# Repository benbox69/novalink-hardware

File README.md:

# NovaLink V1

**Galvanically isolated ESP32-C3 interface for Micronova-controlled pellet stoves (NAVEL INSIDE port).**

NovaLink plugs into the 3-pin service port of a Micronova stove board (designed for X100 EVO "NAVEL INSIDE" connector,
+5 V / SER / GND, 19200 baud single-wire serial) and lets an ESP32-C3 SuperMini talk to the stove through a
3.75 kV digital isolator. The stove side is powered by the stove itself; the ESP side is powered by USB-C.
An optional VL53L0X or VL6180X (TOF050C module) time-of-flight sensor can be connected (for example to measure the pellet level).

An isolated dry-contact output (J4) drives the stove's external thermostat input (TERM), so that Home
Assistant can regulate on a room sensor placed away from the stove.

> ⚠️ **Status: V1 boards built and running on a Micronova X100 EVO: stove reading, stove control and the ToF sensor
> work. The thermostat output (J4) is not tested yet. The enclosure needs rework (see Enclosure).**
>
> This is a hobby project, not affiliated with or endorsed by Micronova. Opening a stove and connecting to its
> controller is at your own risk and may void the warranty.

## Compatibility

- **NAVEL INSIDE port** (3 pins: +5 V, SER, GND), e.g. Micronova X100 EVO: direct connection to J1.
- **SERIAL port** of other Micronova boards: should work too, through an adapter cable to J1
  (J1 pin 1 = +5 V, pin 2 = SER, pin 3 = GND). The firmware must then use the SERIAL port settings
  (usually 1200 baud, 8N2) instead of 19200 baud. Not tested yet.

> 🔴 **Never connect the 20 V line of the SERIAL port.** The SERIAL connector carries an extra supply line
> (about 15–20 V) next to +5 V, SER and GND. Only +5 V, SER and GND go to NovaLink: 20 V on J1 pin 1 would destroy
> the stove side of the board (the isolator supply is limited to 5.5 V, 6 V absolute maximum) and could damage the stove controller.
> Pin order differs between boards: identify each pin with a multimeter before wiring.

## Features

- **Isolation**: CA-IS3721HS digital isolator (Chipanalog), 3750 Vrms, 1 channel each way, fail-safe output high
  (if the ESP is unpowered, the stove line is left idle). 4 mm copper-free barrier with 1 mm milled slots under the
  isolator and under the thermostat relay (each slot runs 1.5 mm past both ends of its package to lengthen the creepage path). Separate grounds `GND_ESP` / `GND_STOVE`.
- **Stove line (SER)**: open-drain style transmit through an SS14 Schottky diode (the board only pulls SER low),
  receive through a 1 kΩ resistor. No TVS on SER on purpose: the line is only pulled up by ~38 kΩ inside the stove,
  extra capacitance would slow the edges.
- **ESP32-C3 SuperMini** (hand soldered), its edge flush with the board edge so the USB-C protrudes by 1.3 mm.
- **ToF sensor connector** (JST XH 5 pins) with 2.2 kΩ I²C pull-ups and 100 Ω series resistors on the cable lines.
- **Extension header** (7 pins, 2.54 mm): GPIO0, GPIO1, I²C, 3V3, GND, 5V (USB).
- **Status LED** on GPIO10, test points for TX, RX, 5V, SER and GND.
- **Thermostat output**: Omron G3VM-61VY3 MOSFET relay (3.75 kVrms, 60 V, 0.7 A), normally open dry contact
  on J4 for the stove TERM input, driven by GPIO3 (removed from J3).
- 89 × 30 mm, 2 layers, all SMD parts in 0805 / SOIC / SOP / SMA (hand-solderable).
- 3D-printable enclosure with captive M3 nuts, magnets and a snap-fit lid.

## Repository layout

| Path | Content |
|---|---|
| `NovaLink.kicad_*` | KiCad 10 project (schematic, PCB) |
| `libs/` | Project library: CA-IS3721HS, G3VM-61VY3 and ESP32-C3 SuperMini symbols, ESP32-C3 SuperMini footprint |
| `production/` | Manufacturing files: `NovaLink.zip` (Gerbers + drill), `bom.csv`, `positions.csv` |
| `docs/` | Schematic PDF, PCB renders, board STEP |
| `enclosure/` | Enclosure: STL, multi-colour 3MF and STEP files |

## Schematic

[docs/NovaLink_schematic.pdf](docs/NovaLink_schematic.pdf) — one A4 sheet, six blocks: ESP32-C3 SuperMini and LED,
isolation and stove connector, test points and mounting holes, ToF sensor, extension header, thermostat output.

### ESP32-C3 SuperMini pins

| Function | GPIO | Notes |
|---|---|---|
| TX to stove | GPIO5 | UART1 TX (GPIO21 is avoided: it prints the ROM boot log) |
| RX from stove | GPIO20 | UART1 RX |
| I²C SDA / SCL | GPIO6 / GPIO7 | shared between J2 and J3 |
| Sensor XSHUT | GPIO4 | |
| Status LED | GPIO10 | active high |
| Thermostat output | GPIO3 | high = contact closed |
| On J3 only | GPIO0, GPIO1 | |
| Unused | GPIO2, GPIO8, GPIO9, GPIO21 | strapping / boot pins |

### Connectors

| Ref | Type | Pinout |
|---|---|---|
| J1 (stove) | JST XH 3 pins, right angle | 1 = +5V, 2 = SER, 3 = GND (stove side, isolated) |
| J2 (ToF sensor) | JST XH 5 pins, right angle | 1 = 3V3, 2 = GND, 3 = SDA, 4 = SCL, 5 = XSHUT |
| J3 (extension) | 1×7 pin header 2.54 mm | IO0, IO1, SDA, SCL, 3V3, GND, 5V (USB, not isolated) |
| J4 (stove TERM) | JST XH 2 pins, right angle | 1, 2 = dry contact to the stove TERM input, no polarity (isolated) |

## Bill of materials

[production/bom.csv](production/bom.csv) (values, packages, LCSC part numbers). U1, the ESP32-C3 SuperMini
(U.FL version recommended), is not in the file: it is hand soldered.

## Thermostat output

Micronova boards have an external thermostat input (TERM, a normally open dry contact). On the boards documented by
Micronova (I023, N100), the contact works as follows:

| J4 contact | STAND-BY off (default) | STAND-BY on |
|---|---|---|
| Closed (GPIO3 high) | WORK at the set power | WORK |
| Open (GPIO3 low, ESP off) | MODULATION (minimum power, flame on) | MODULATION, then shutdown after Pr44, restart when the contact closes |

The stove still heats while its own room probe is below its set point (probe **or** contact). To let the contact
alone decide, set the stove set point to 7 °C; a higher value (for example 15 °C) keeps the stove probe as a backup
if Home Assistant or the ESP fails.

> ⚠️ Not yet checked on the X100 EVO.

## Enclosure

> ⚠️ **This enclosure needs rework: do not print it yet.**

Ready-to-print files in `enclosure/`: `NovaLink_enclosure_base.stl`, `NovaLink_enclosure_lid.stl`,
`NovaLink_enclosure_led_window.stl` and `NovaLink_enclosure_j3_cover.stl`. For a multi-colour printer:
`NovaLink_enclosure_base_multicolor.3mf` (base + white connector names, also as
`NovaLink_enclosure_base_labels.stl`) and `NovaLink_enclosure_lid_multicolor.3mf` (lid + clear LED window),
one filament per body.
`NovaLink_enclosure.step` to adapt the enclosure in any CAD tool. The enclosure was checked against the
KiCad 3D model of the board (`docs/NovaLink.step`): no interference.

- Outside 94 × 33.8 × 22.5 mm, openings for USB-C (tight rounded opening, the receptacle is flush with the 1.2 mm
  front wall), J2 (sensor) and J1 + J4 (stove, TERM), slot above J3.
- Small cover closing the J3 slot when the header is not used: flush in a recess of the lid, friction fit,
  fingernail notch to remove it.
- Board held by two M3 × 10 screws into M3 nuts caged inside the base, plus a support peg. Pause the print at Z = 3.0 mm (top of the hexagonal pockets), drop an M3 nut in each pocket, then resume: the nuts end up fully enclosed (closed 0.4 mm skin below, no hole through the underside). M3 × 10 is the longest screw that fits: 10.2 mm from the board top down to the skin.
- 4 pockets for Ø10 × 3 mm magnets to stick the box to the back of the stove.
- Snap-fit lid, removable with a flat screwdriver (notch at the front).
- Connector names on the front wall, under the openings: 0.4 mm inlay in a second colour (or plain engraving
  with a single-colour printer).
- Lid: engraved name, vent slots, flexible reset key (round pad on a thin beam, pusher on the SuperMini RST
  button, the one on the J3 side) and a transparent light pipe above the status LED, in an opaque sleeve.
- Print the lid top face down, in **PETG or ASA**, not PLA (the back of a stove gets warm); LED window in clear PETG,
  J3 cover cap face down.

## Firmware

The firmware is an ESPHome external component, in its own repository:
[benbox69/novalink-firmware](https://github.com/benbox69/novalink-firmware). It reads the stove, controls it (on/off,
setpoint, power level) and runs a protection in the board itself. A ready-to-use configuration for this board is in
its `examples/` folder.

No pin inversion is needed (the isolator and the diode keep the logic levels). 19200 baud is for the NAVEL INSIDE port;
the SERIAL port usually uses 1200 baud, 8N2 (see Compatibility).

> ⚠️ On the X100 EVO, never write to RAM address 0x58: it raises the "fumes probe" alarm.

## 3D model of the SuperMini

The ESP32-C3 SuperMini 3D model is not included. Download it (CC0) from
[Printables – ESP32 C3 Super mini model by Josselin Hefti](https://printables.com/model/1360390-esp32-c3-super-mini-model)
and save the STEP file as `libs/3d/ESP32-C3-SuperMini.step`; the footprint already points to it.

## License

NovaLink (hardware design, enclosure and documentation) is licensed under
[Creative Commons Attribution-NonCommercial-ShareAlike 4.0](https://creativecommons.org/licenses/by-nc-sa/4.0/)
(CC BY-NC-SA 4.0): you may build, modify and share it for non-commercial purposes, with attribution and under the
same license. Commercial use or sale is not permitted.

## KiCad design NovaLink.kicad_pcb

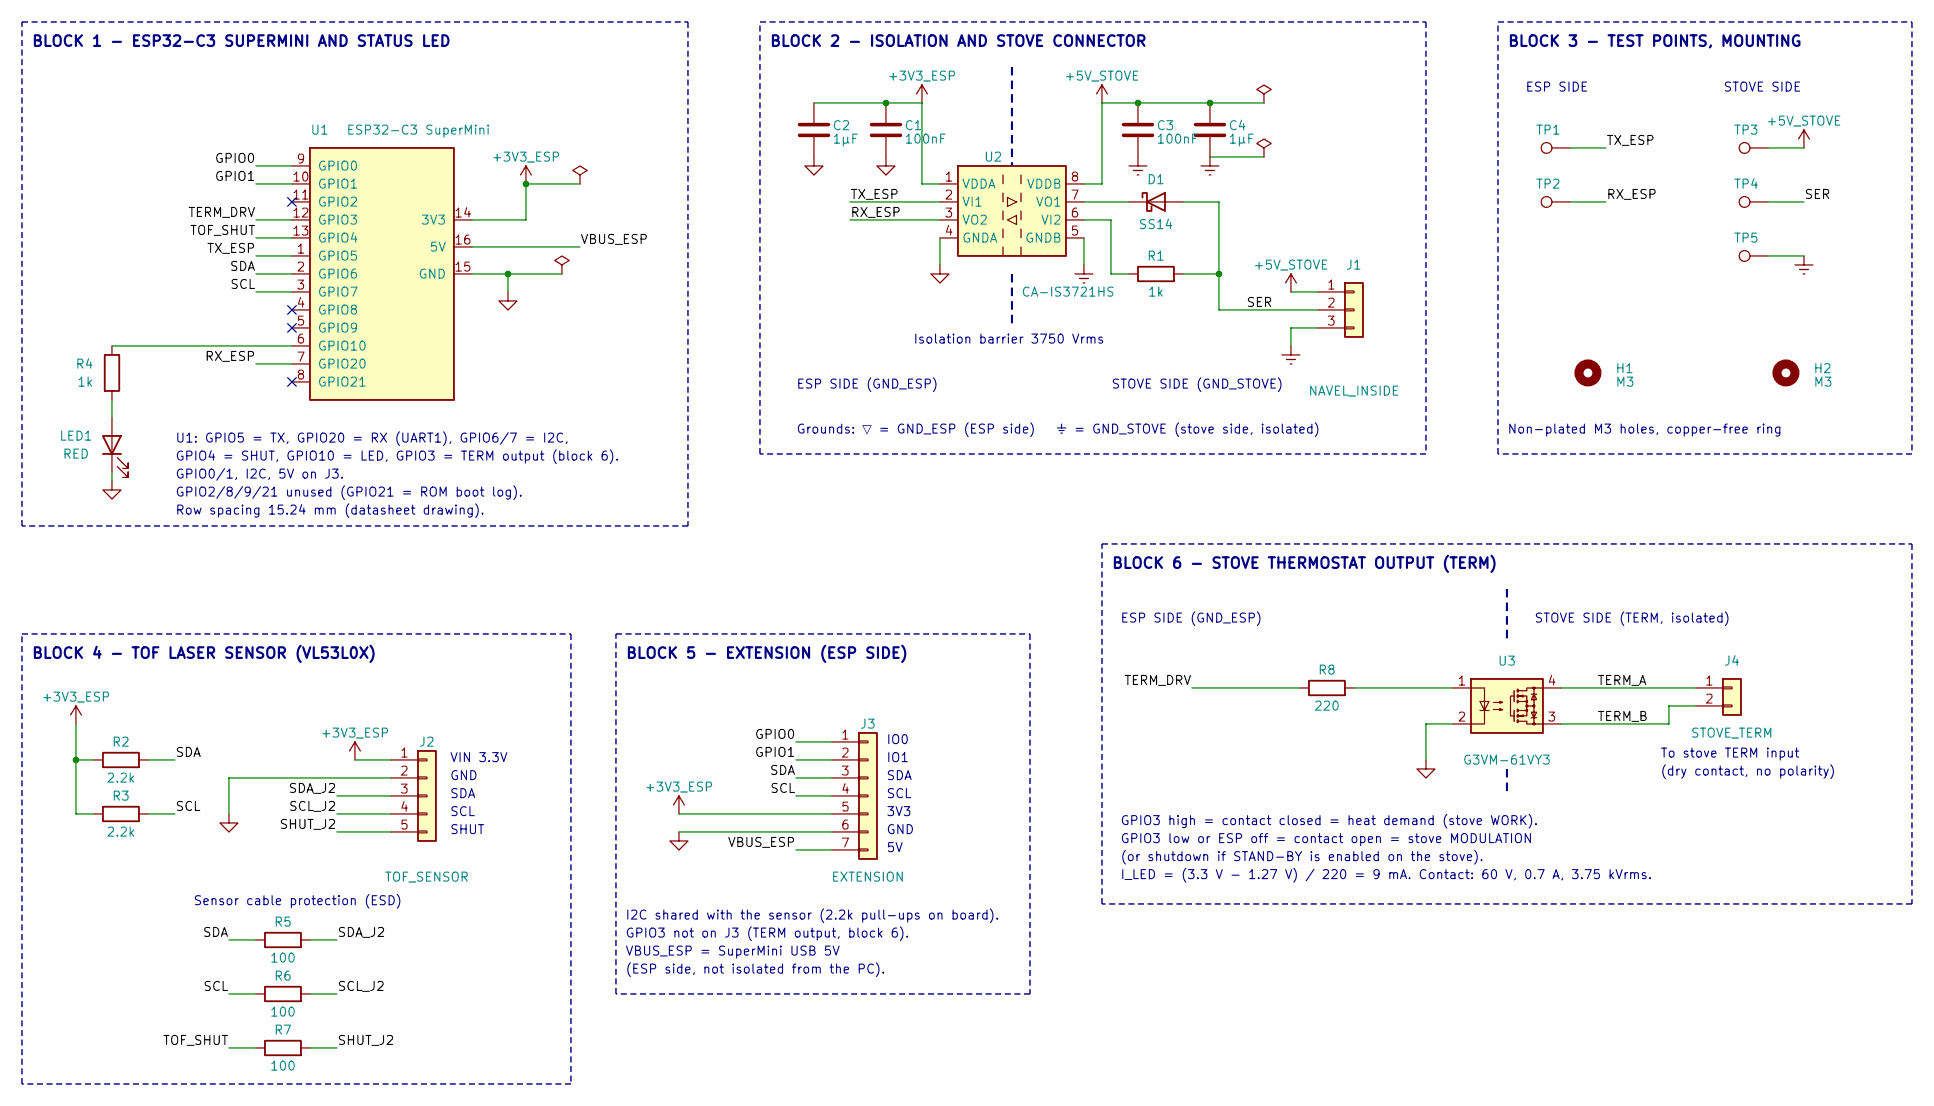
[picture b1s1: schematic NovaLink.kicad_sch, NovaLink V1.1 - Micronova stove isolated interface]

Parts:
C1, C3: 100nF; C_0805_2012Metric_Pad1.18x1.45mm_HandSolder; LCSC Part # C49678
C2, C4: 1µF; C_0805_2012Metric_Pad1.18x1.45mm_HandSolder; LCSC Part # C28323
D1: SS14; D_SMA; MPN SS14; LCSC Part # C2480
H1, H2: M3; MountingHole_3.2mm_M3
J1: NAVEL_INSIDE; JST_XH_S3B-XH-A_1x03_P2.50mm_Horizontal; MPN S3B-XH-A(LF)(SN); LCSC Part # C157928
J2: TOF_SENSOR; JST_XH_S5B-XH-A_1x05_P2.50mm_Horizontal; MPN S5B-XH-A(LF)(SN); LCSC Part # C263757
J3: EXTENSION; PinHeader_1x07_P2.54mm_Vertical; MPN PZ254V-11-07P; LCSC Part # C492406
J4: STOVE_TERM; JST_XH_S2B-XH-A_1x02_P2.50mm_Horizontal; MPN S2B-XH-A(LF)(SN); LCSC Part # C157931
LED1: RED; LED_0805_2012Metric_Pad1.15x1.40mm_HandSolder; MPN NCD0805R1; LCSC Part # C84256
R1, R4: 1k; R_0805_2012Metric_Pad1.20x1.40mm_HandSolder; MPN 0805W8F1001T5E; LCSC Part # C17513
R2, R3: 2.2k; R_0805_2012Metric_Pad1.20x1.40mm_HandSolder; LCSC Part # C17520
R5, R6, R7: 100; R_0805_2012Metric_Pad1.20x1.40mm_HandSolder; MPN 0805W8F1000T5E; LCSC Part # C17408
R8: 220; R_0805_2012Metric_Pad1.20x1.40mm_HandSolder; MPN 0805W8F2200T5E; LCSC Part # C17557
TP1: TX_ESP; TestPoint_THTPad_D1.5mm_Drill0.7mm
TP2: RX_ESP; TestPoint_THTPad_D1.5mm_Drill0.7mm
TP3: +5V_STOVE; TestPoint_THTPad_D1.5mm_Drill0.7mm
TP4: SER; TestPoint_THTPad_D1.5mm_Drill0.7mm
TP5: GND_STOVE; TestPoint_THTPad_D1.5mm_Drill0.7mm
U1: ESP32-C3 SuperMini; ESP32-C3-SuperMini; MPN ESP32-C3 SuperMini
U2: CA-IS3721HS; SOIC-8_3.9x4.9mm_P1.27mm; MPN CA-IS3721HS; LCSC Part # C428884
U3: G3VM-61VY3; SO-4_4.4x3.6mm_P2.54mm; MPN G3VM-61VY3(TR); LCSC Part # C2152318

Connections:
+3V3_ESP: C1.1, C2.1, J2.1, J3.5, R2.1, R3.1, U1.14 (3V3), U2.1 (VDDA)
+5V_STOVE: C3.1, C4.1, J1.1, TP3.1, U2.8 (VDDB)
/GPIO0: J3.1, U1.9 (GPIO0)
/GPIO1: J3.2, U1.10 (GPIO1)
/RX_ESP: TP2.1, U1.7 (GPIO20), U2.3 (VO2)
/SCL: J3.4, R3.2, R6.1, U1.3 (GPIO7)
/SCL_J2: J2.4, R6.2
/SDA: J3.3, R2.2, R5.1, U1.2 (GPIO6)
/SDA_J2: J2.3, R5.2
/SER: D1.2 (A), J1.2, R1.2, TP4.1
/SHUT_J2: J2.5, R7.2
/TERM_A: J4.1, U3.4
/TERM_B: J4.2, U3.3
/TERM_DRV: R8.1, U1.12 (GPIO3)
/TOF_SHUT: R7.1, U1.13 (GPIO4)
/TX_ESP: TP1.1, U1.1 (GPIO5), U2.2 (VI1)
/VBUS_ESP: J3.7, U1.16 (5V)
GND_ESP: C1.2, C2.2, J2.2, J3.6, LED1.1 (K), U1.15 (GND), U2.4 (GNDA), U3.2
GND_STOVE: C3.2, C4.2, J1.3, TP5.1, U2.5 (GNDB)
unnamed: D1.1 (K), U2.7 (VO1)
unnamed: LED1.2 (A), R4.2
unnamed: R8.2, U3.1
unnamed: R4.1, U1.6 (GPIO10)
unnamed: R1.1, U2.6 (VI2)

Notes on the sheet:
BLOCK 1 - ESP32-C3 SUPERMINI AND STATUS LED
U1: GPIO5 = TX, GPIO20 = RX (UART1), GPIO6/7 = I2C,
GPIO4 = SHUT, GPIO10 = LED, GPIO3 = TERM output (block 6).
GPIO0/1, I2C, 5V on J3.
GPIO2/8/9/21 unused (GPIO21 = ROM boot log).
Row spacing 15.24 mm (datasheet drawing).
BLOCK 2 - ISOLATION AND STOVE CONNECTOR
ESP SIDE (GND_ESP)
STOVE SIDE (GND_STOVE)
Isolation barrier 3750 Vrms
Grounds: ▽ = GND_ESP (ESP side) ⏚ = GND_STOVE (stove side, isolated)
BLOCK 3 - TEST POINTS, MOUNTING
ESP SIDE
STOVE SIDE
Non-plated M3 holes, copper-free ring
BLOCK 4 - TOF LASER SENSOR (VL53L0X)
VIN 3.3V
GND
SDA
SCL
SHUT
Sensor cable protection (ESD)
BLOCK 5 - EXTENSION (ESP SIDE)
IO0
IO1
3V3
I2C shared with the sensor (2.2k pull-ups on board).
GPIO3 not on J3 (TERM output, block 6).
VBUS_ESP = SuperMini USB 5V
(ESP side, not isolated from the PC).
BLOCK 6 - STOVE THERMOSTAT OUTPUT (TERM)
STOVE SIDE (TERM, isolated)
To stove TERM input
(dry contact, no polarity)
GPIO3 high = contact closed = heat demand (stove WORK).
GPIO3 low or ESP off = contact open = stove MODULATION
(or shutdown if STAND-BY is enabled on the stove).
I_LED = (3.3 V - 1.27 V) / 220 = 9 mA. Contact: 60 V, 0.7 A, 3.75 kVrms.

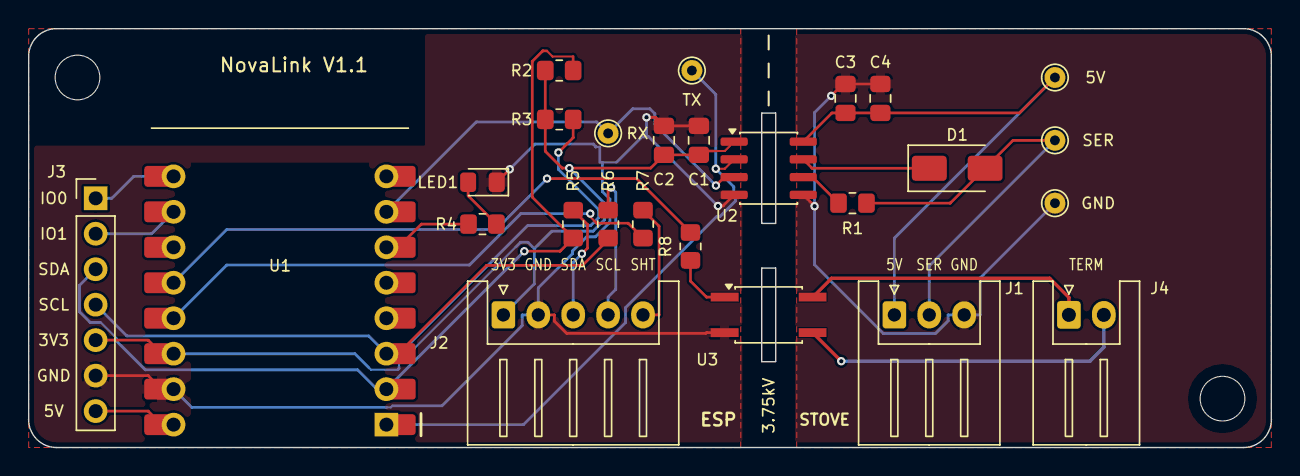
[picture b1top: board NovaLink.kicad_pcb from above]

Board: 2 copper layers, 89.0 x 30.0 mm, 28 parts (0 on the bottom side), 24 nets.

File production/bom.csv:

Designator,Footprint,Quantity,Value,LCSC Part #
"C1, C3",0805,2,100nF,C49678
"C2, C4",0805,2,1µF,C28323
D1,D_SMA,1,SS14,C2480
J1,JST_XH_S3B-XH-A_1x03_P2.50mm_Horizontal,1,NAVEL_INSIDE,C157928
J2,JST_XH_S5B-XH-A_1x05_P2.50mm_Horizontal,1,TOF_SENSOR,C263757
J3,PinHeader_1x07_P2.54mm_Vertical,1,EXTENSION,C492406
J4,JST_XH_S2B-XH-A_1x02_P2.50mm_Horizontal,1,STOVE_TERM,C157931
LED1,0805,1,RED,C84256
"R1, R4",0805,2,1k,C17513
"R2, R3",0805,2,2.2k,C17520
"R5, R6, R7",0805,3,100,C17408
R8,0805,1,220,C17557
U2,SOIC-8_3.9x4.9mm_P1.27mm,1,CA-IS3721HS,C428884
U3,SO-4_4.4x3.6mm_P2.54mm,1,G3VM-61VY3,C2152318

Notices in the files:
NovaLink.kicad_pcb:
License: CC BY-NC-SA 4.0
